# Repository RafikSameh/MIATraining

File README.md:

# MIATraining
 online training tasks

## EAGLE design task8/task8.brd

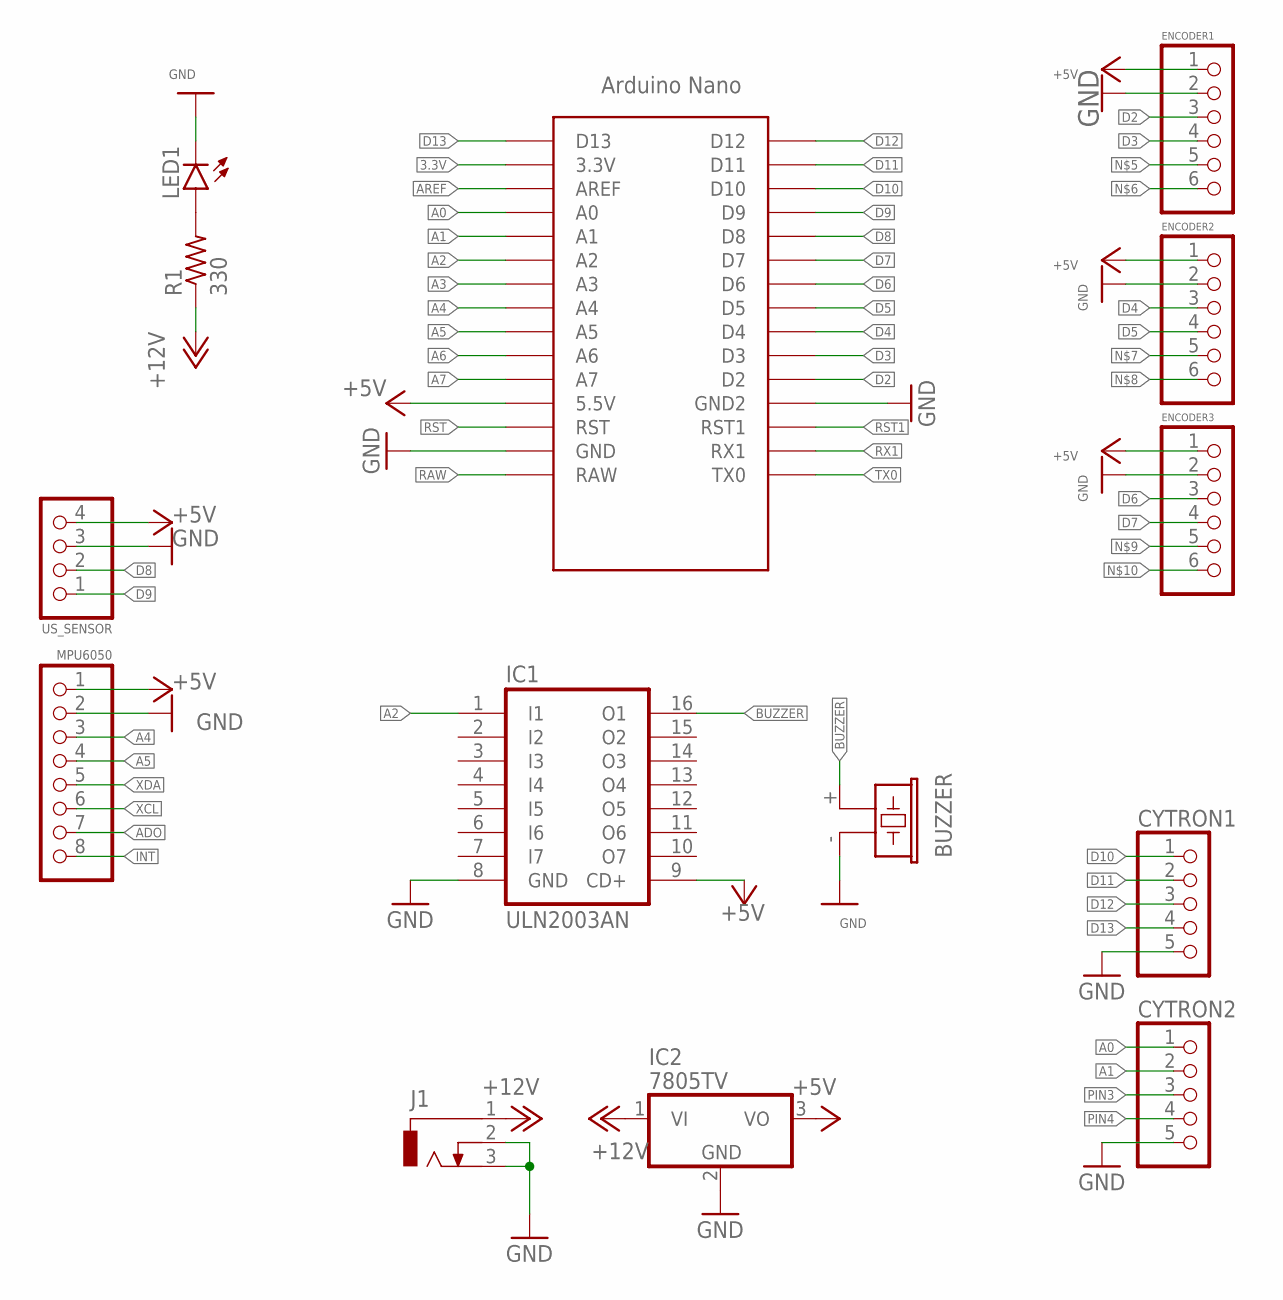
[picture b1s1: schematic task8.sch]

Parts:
CYTRON1, CYTRON2: PINHD-1X5; 1X05
ENCODER1, ENCODER2, ENCODER3: PINHD-1X6; 1X06
IC1: ULN2003AN; DIL16
IC2: 7805TV; TO220V
J1: CON_JACK; DCJ0303
LED1: LED5MM
MPU6050: PINHD-1X8; 1X08
R1: 330; 0204/7
SG1: BUZZER; F/CM12P
U$1: ARDUINO_NANO; NANO
US_SENSOR: PINHD-1X4; 1X04

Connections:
3.3V: U$1.3.3V
+5V: ENCODER1.1, ENCODER2.1, ENCODER3.1, IC1.9 (CD+), IC2.3 (VO), MPU6050.1, U$1.5V (5.5V), US_SENSOR.4
+12V: IC2.1 (VI), J1.1, R1.1
A0: CYTRON2.1, U$1.A0
A1: CYTRON2.2, U$1.A1
A2: IC1.1 (I1), U$1.A2
A3: U$1.A3
A4: MPU6050.3, U$1.A4
A5: MPU6050.4, U$1.A5
A6: U$1.A6
A7: U$1.A7
ADO: MPU6050.7
AREF: U$1.AREF
BUZZER: IC1.16 (O1), SG1.+ (1)
D2: ENCODER1.3, U$1.D2
D3: ENCODER1.4, U$1.D3
D4: ENCODER2.3, U$1.D4
D5: ENCODER2.4, U$1.D5
D6: ENCODER3.3, U$1.D6
D7: ENCODER3.4, U$1.D7
D8: U$1.D8, US_SENSOR.2
D9: U$1.D9, US_SENSOR.1
D10: CYTRON1.1, U$1.D10
D11: CYTRON1.2, U$1.D11
D12: CYTRON1.3, U$1.D12
D13: CYTRON1.4, U$1.D13
GND: CYTRON1.5, CYTRON2.5, ENCODER1.2, ENCODER2.2, ENCODER3.2, IC1.8 (GND), IC2.2 (GND), J1.2, J1.3, LED1.K (C), MPU6050.2, SG1.- (2), U$1.GND, U$1.GND1 (GND2), US_SENSOR.3
INT: MPU6050.8
unnamed: LED1.A, R1.2
PIN3: CYTRON2.3
PIN4: CYTRON2.4
RAW: U$1.RAW
RST: U$1.RST
RST1: U$1.RST1
RX1: U$1.RX1
TX0: U$1.TX0
XCL: MPU6050.6
XDA: MPU6050.5

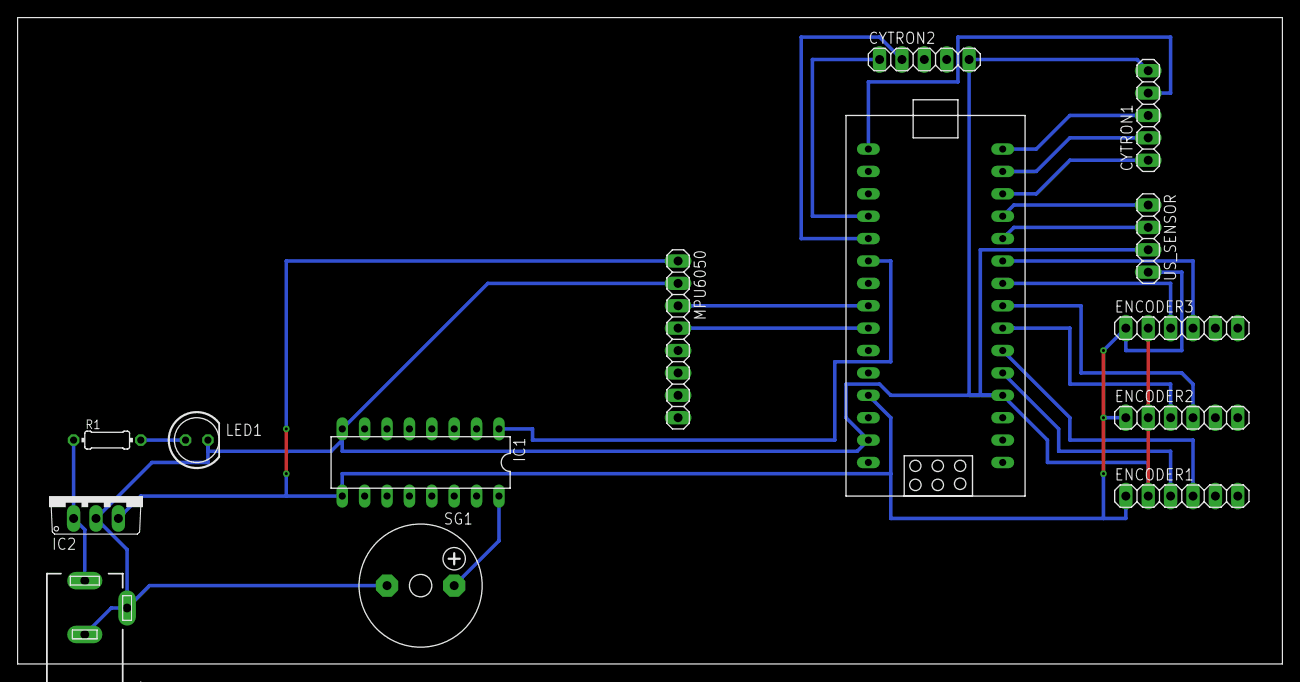
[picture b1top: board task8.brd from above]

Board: 2 copper layers, 143.5 x 73.3 mm, 14 parts (0 on the bottom side), 22 nets.

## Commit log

2022-08-11 task1
    projects1,2,3,4
2022-08-11 task2
    robot rental system
2022-08-11 task3
    hardware projects
2022-08-11 task4
    arduino projects
2022-08-11 delete
2022-08-11 task1
    c++ projects 1,2,3,4
2022-08-11 task3
    hardware project
2022-08-11 task3
2022-08-11 task1 remove from task3
2022-08-11 task4 upload
    remove other tasks from these branch
2022-08-23 sequential code
    please ! read the comment
2022-08-23 oop codes
2022-08-29 linux tasak
2022-08-31 sensors task
2022-09-02 task5
2022-09-07 pcb task
